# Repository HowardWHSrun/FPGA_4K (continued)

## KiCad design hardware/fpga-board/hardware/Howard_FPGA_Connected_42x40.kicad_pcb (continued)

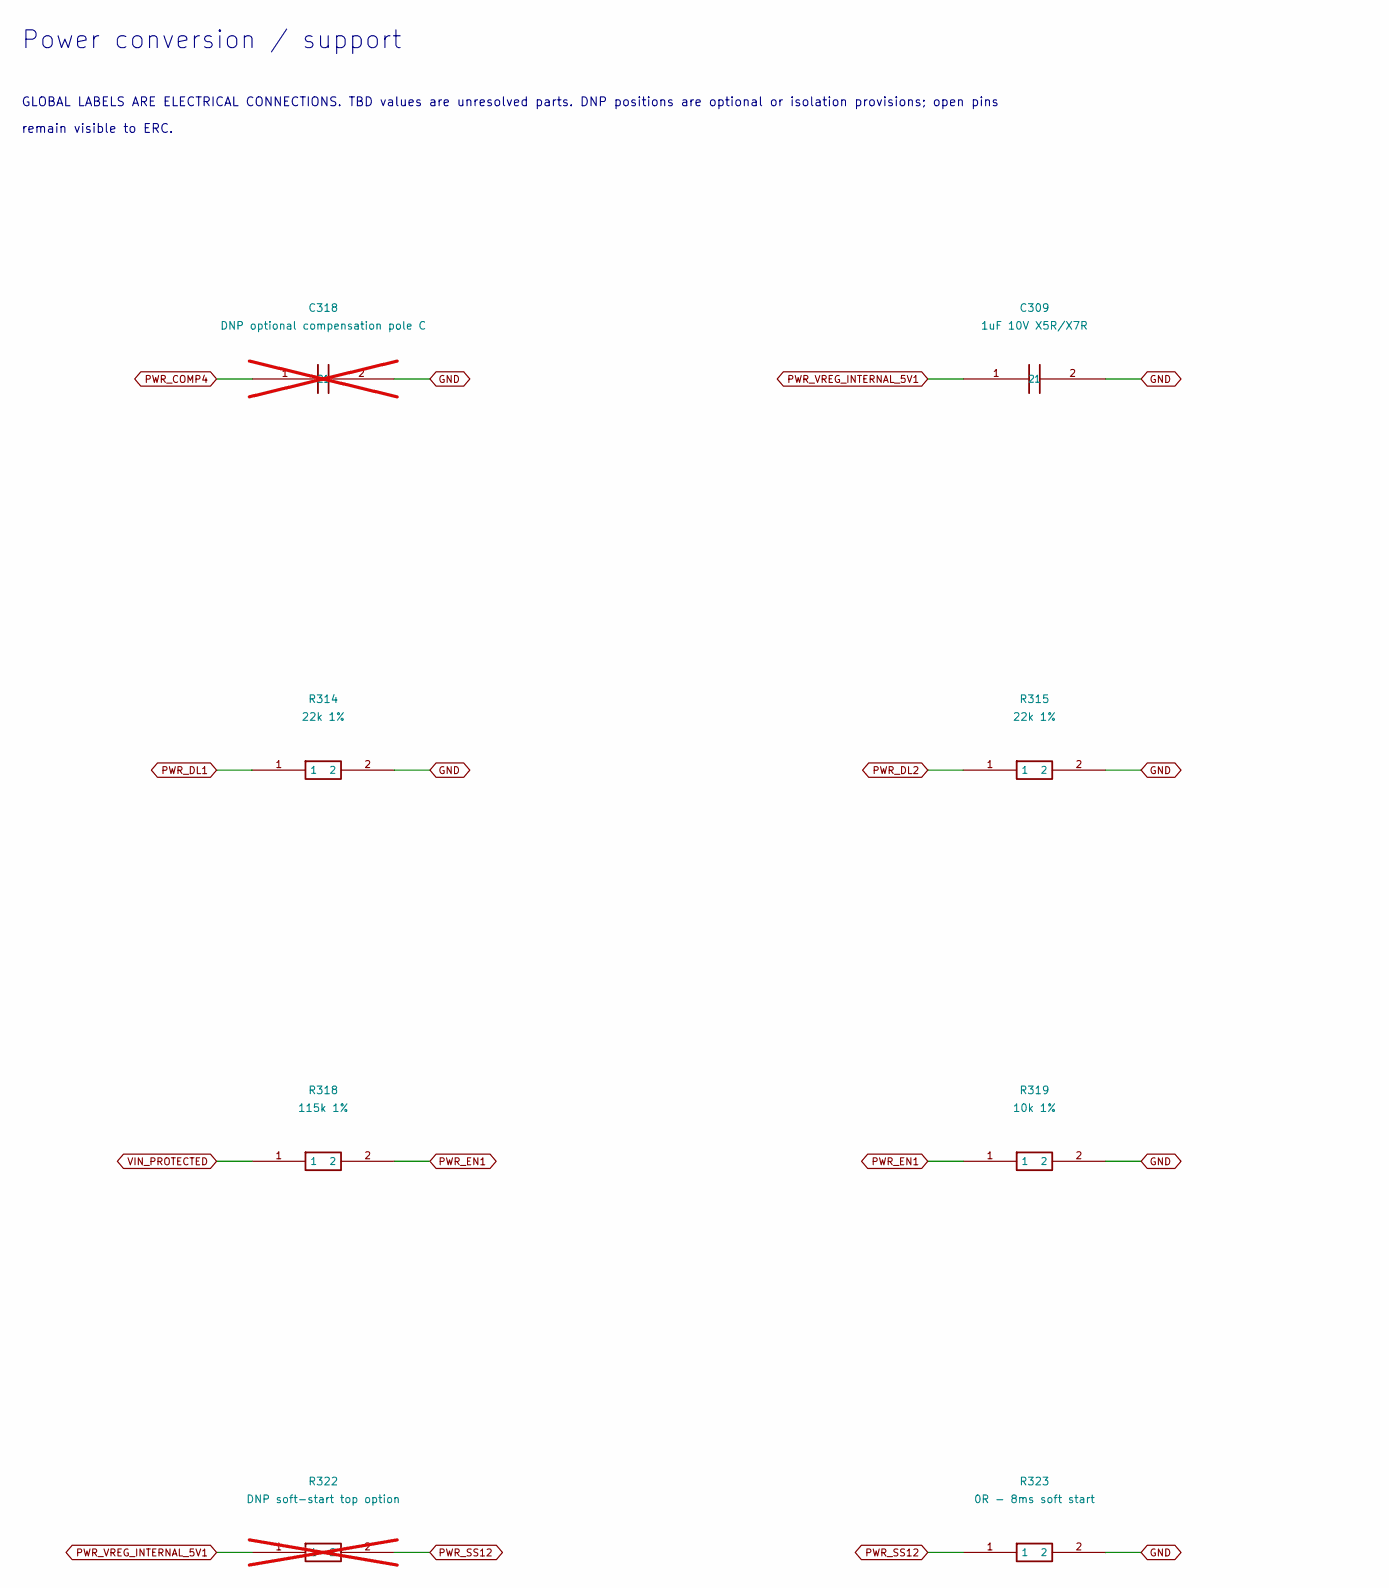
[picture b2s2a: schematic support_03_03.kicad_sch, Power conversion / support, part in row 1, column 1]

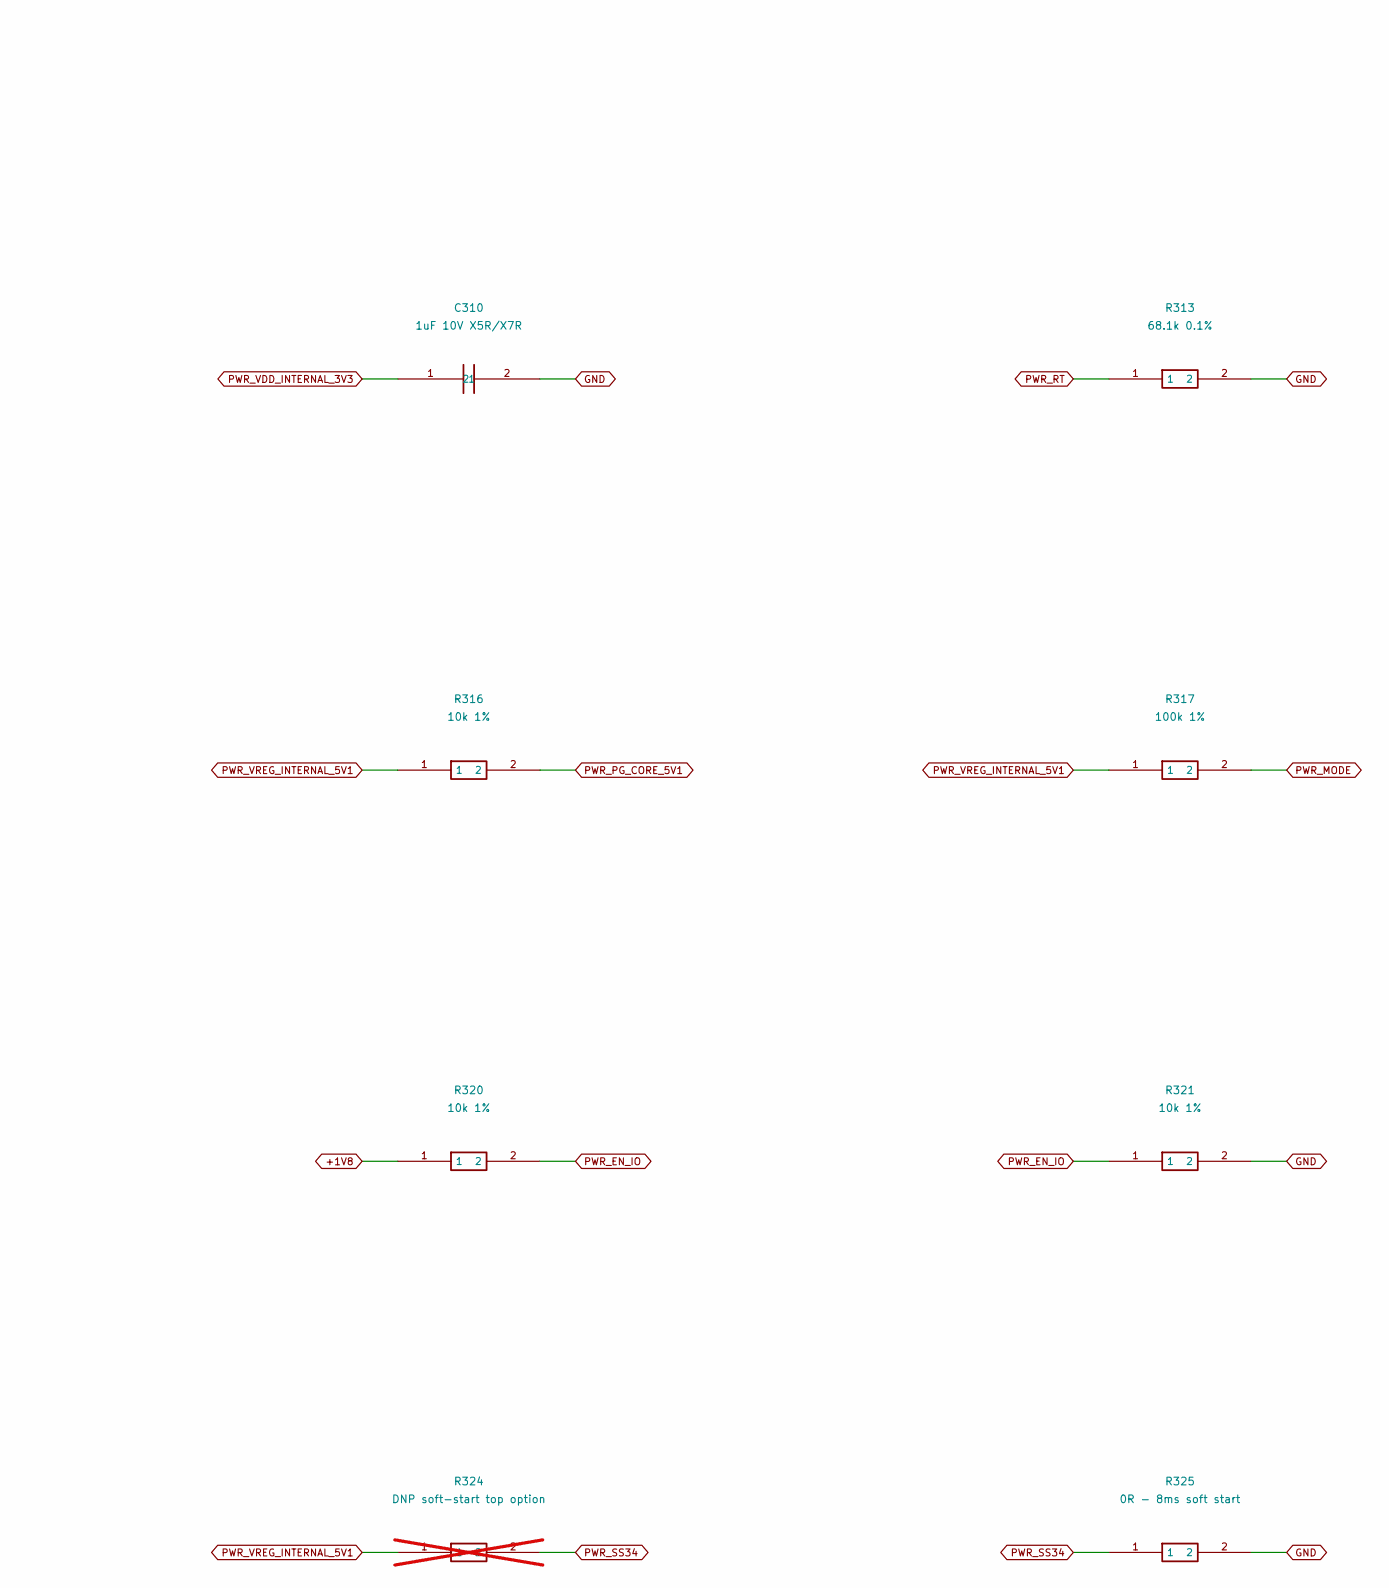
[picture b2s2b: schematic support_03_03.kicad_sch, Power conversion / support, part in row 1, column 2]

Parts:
C309: 1uF 10V X5R/X7R; C_0402_1005Metric__C309; Tolerance TBD; Voltage rating TBD; MPN TBD
C310: 1uF 10V X5R/X7R; C_0402_1005Metric__C310; Tolerance TBD; Voltage rating TBD; MPN TBD
C318: DNP optional compensation pole C; C_0402_1005Metric__C318; Tolerance TBD; Voltage rating TBD; MPN TBD; not fitted
R313: 68.1k 0.1%; R_0402_1005Metric__R313; Tolerance TBD; Voltage rating TBD; MPN TBD
R314: 22k 1%; R_0402_1005Metric__R314; Tolerance TBD; Voltage rating TBD; MPN TBD
R315: 22k 1%; R_0402_1005Metric__R315; Tolerance TBD; Voltage rating TBD; MPN TBD
R316: 10k 1%; R_0402_1005Metric__R316; Tolerance TBD; Voltage rating TBD; MPN TBD
R317: 100k 1%; R_0402_1005Metric__R317; Tolerance TBD; Voltage rating TBD; MPN TBD
R318: 115k 1%; R_0402_1005Metric__R318; Tolerance TBD; Voltage rating TBD; MPN TBD
R319: 10k 1%; R_0402_1005Metric__R319; Tolerance TBD; Voltage rating TBD; MPN TBD
R320: 10k 1%; R_0402_1005Metric__R320; Tolerance TBD; Voltage rating TBD; MPN TBD
R321: 10k 1%; R_0402_1005Metric__R321; Tolerance TBD; Voltage rating TBD; MPN TBD
R322: DNP soft-start top option; R_0402_1005Metric__R322; Tolerance TBD; Voltage rating TBD; MPN TBD; not fitted
R323: 0R - 8ms soft start; R_0402_1005Metric__R323; Tolerance TBD; Voltage rating TBD; MPN TBD
R324: DNP soft-start top option; R_0402_1005Metric__R324; Tolerance TBD; Voltage rating TBD; MPN TBD; not fitted
R325: 0R - 8ms soft start; R_0402_1005Metric__R325; Tolerance TBD; Voltage rating TBD; MPN TBD

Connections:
+1V8: R320.1; also elsewhere on the board
GND: C309.2, C310.2, C318.2, R313.2, R314.2, R315.2, R319.2, R321.2, R323.2, R325.2; also elsewhere on the board
PWR_COMP4: C318.1; also elsewhere on the board
PWR_DL1: R314.1; also elsewhere on the board
PWR_DL2: R315.1; also elsewhere on the board
PWR_EN1: R318.2, R319.1; also elsewhere on the board
PWR_EN_IO: R320.2, R321.1; also elsewhere on the board
PWR_MODE: R317.2; also elsewhere on the board
PWR_PG_CORE_5V1: R316.2; also elsewhere on the board
PWR_RT: R313.1; also elsewhere on the board
PWR_SS12: R322.2, R323.1; also elsewhere on the board
PWR_SS34: R324.2, R325.1; also elsewhere on the board
PWR_VDD_INTERNAL_3V3: C310.1; also elsewhere on the board
PWR_VREG_INTERNAL_5V1: C309.1, R316.1, R317.1, R322.1, R324.1; also elsewhere on the board
VIN_PROTECTED: R318.1; also elsewhere on the board

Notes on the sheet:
GLOBAL LABELS ARE ELECTRICAL CONNECTIONS. TBD values are unresolved parts. DNP positions are optional or isolation provisions; open pins
Power conversion / support
remain visible to ERC.

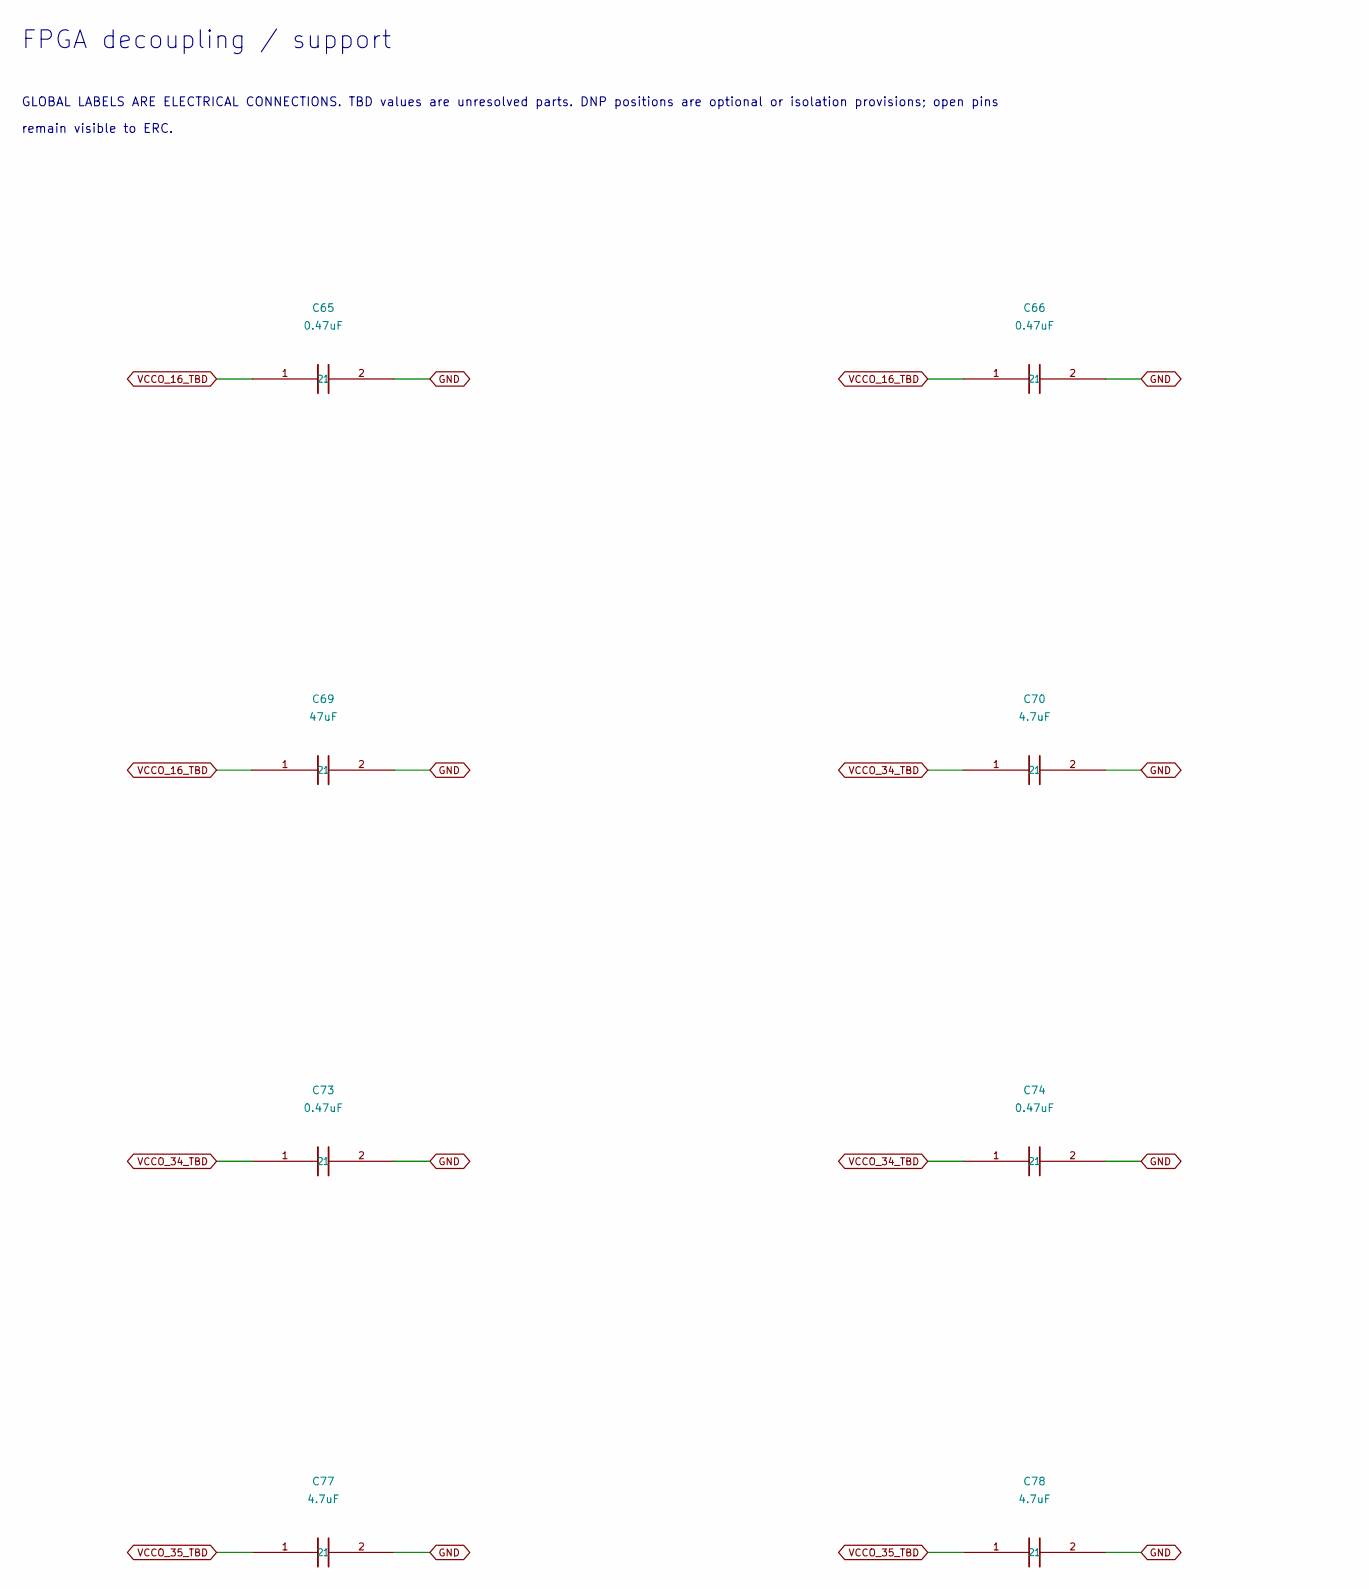
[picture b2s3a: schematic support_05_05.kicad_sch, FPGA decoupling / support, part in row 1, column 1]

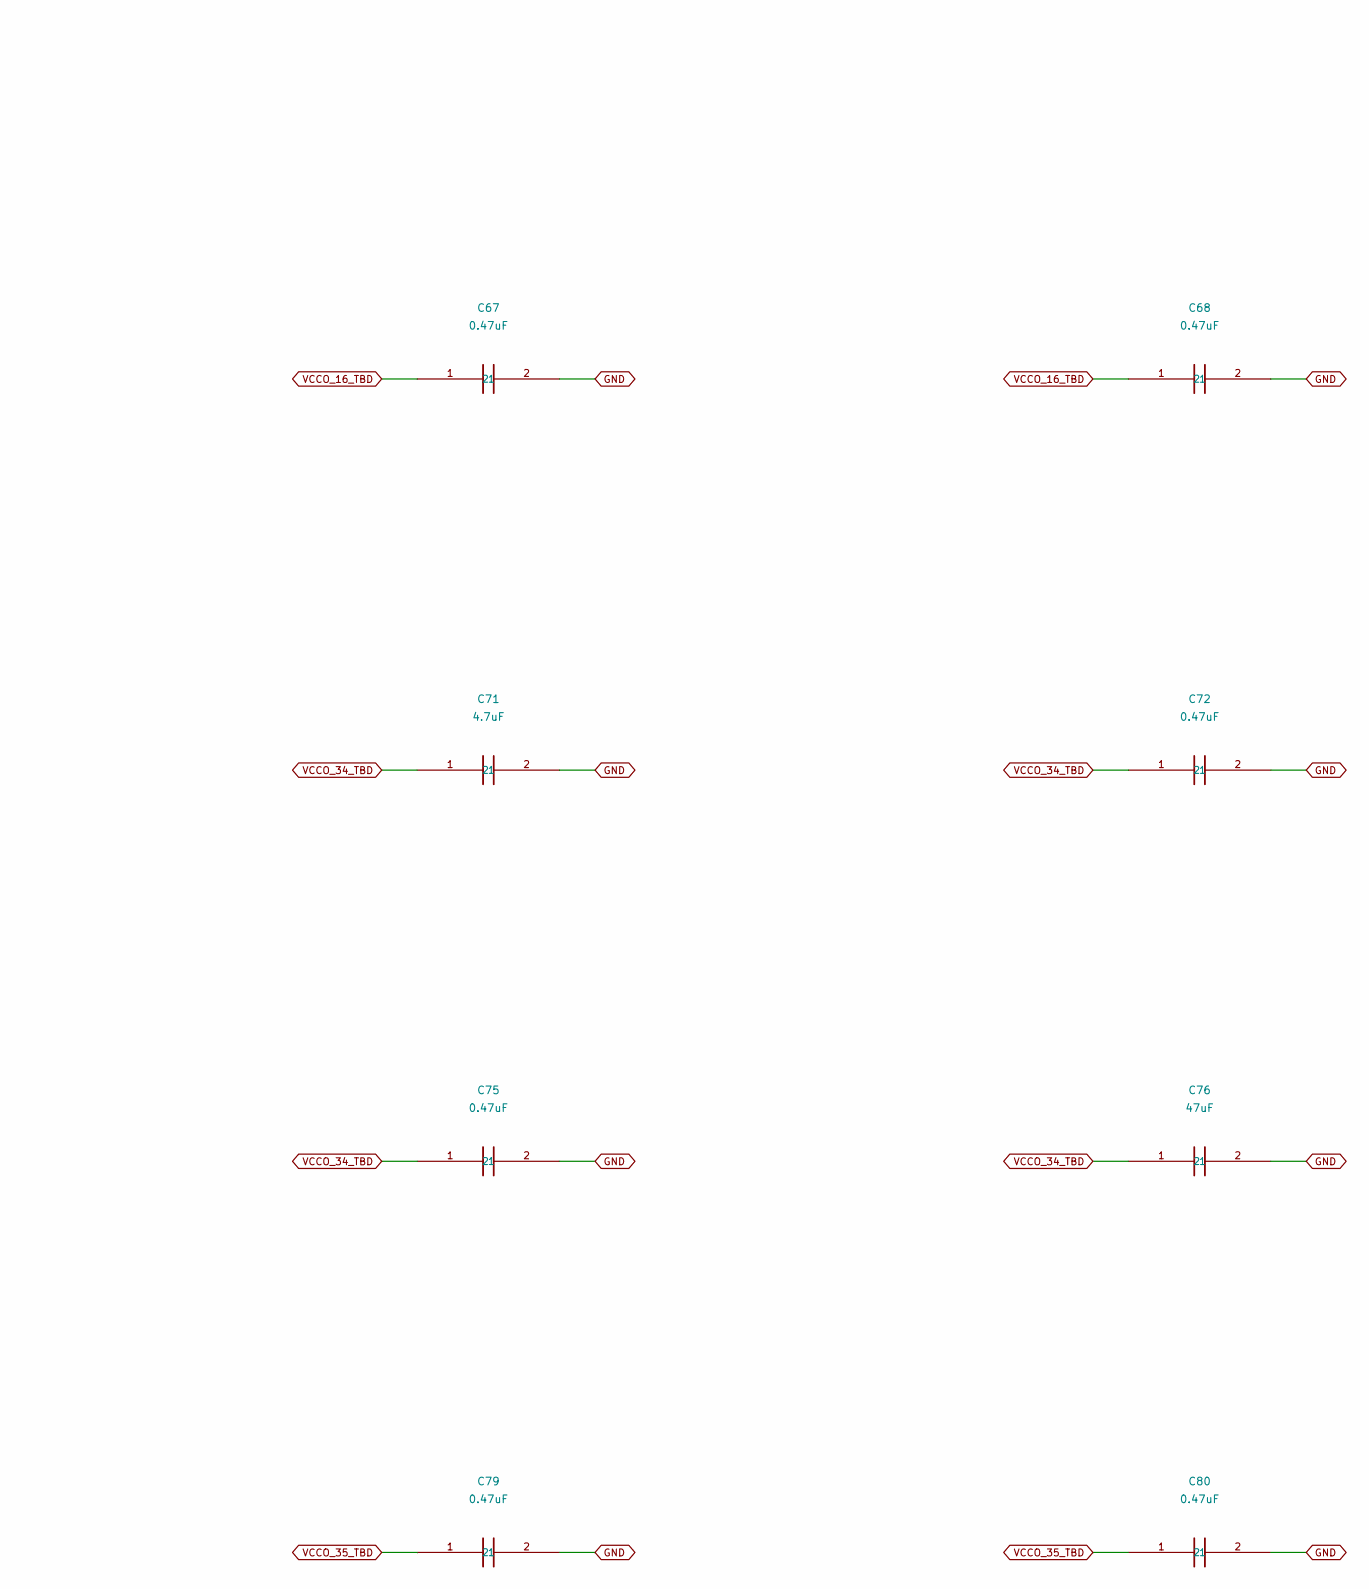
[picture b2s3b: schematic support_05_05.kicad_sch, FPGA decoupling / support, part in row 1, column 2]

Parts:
C65: 0.47uF; C_0201_0603Metric__C65; Tolerance 20%; Voltage rating 10 V; MPN C0603X5R1A474M030BC
C66: 0.47uF; C_0201_0603Metric__C66; Tolerance 20%; Voltage rating 10 V; MPN C0603X5R1A474M030BC
C67: 0.47uF; C_0201_0603Metric__C67; Tolerance 20%; Voltage rating 10 V; MPN C0603X5R1A474M030BC
C68: 0.47uF; C_0201_0603Metric__C68; Tolerance 20%; Voltage rating 10 V; MPN C0603X5R1A474M030BC
C69: 47uF; C_1210_3225Metric__C69; Tolerance TBD; Voltage rating TBD; MPN TBD
C70: 4.7uF; C_0402_1005Metric__C70; Tolerance 10%; Voltage rating 10 V; MPN C1005X5R1A475K050BC
C71: 4.7uF; C_0402_1005Metric__C71; Tolerance 10%; Voltage rating 10 V; MPN C1005X5R1A475K050BC
C72: 0.47uF; C_0201_0603Metric__C72; Tolerance 20%; Voltage rating 10 V; MPN C0603X5R1A474M030BC
C73: 0.47uF; C_0201_0603Metric__C73; Tolerance 20%; Voltage rating 10 V; MPN C0603X5R1A474M030BC
C74: 0.47uF; C_0201_0603Metric__C74; Tolerance 20%; Voltage rating 10 V; MPN C0603X5R1A474M030BC
C75: 0.47uF; C_0201_0603Metric__C75; Tolerance 20%; Voltage rating 10 V; MPN C0603X5R1A474M030BC
C76: 47uF; C_1210_3225Metric__C76; Tolerance TBD; Voltage rating TBD; MPN TBD
C77: 4.7uF; C_0402_1005Metric__C77; Tolerance 10%; Voltage rating 10 V; MPN C1005X5R1A475K050BC
C78: 4.7uF; C_0402_1005Metric__C78; Tolerance 10%; Voltage rating 10 V; MPN C1005X5R1A475K050BC
C79: 0.47uF; C_0201_0603Metric__C79; Tolerance 20%; Voltage rating 10 V; MPN C0603X5R1A474M030BC
C80: 0.47uF; C_0201_0603Metric__C80; Tolerance 20%; Voltage rating 10 V; MPN C0603X5R1A474M030BC

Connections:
GND: C65.2, C66.2, C67.2, C68.2, C69.2, C70.2, C71.2, C72.2, C73.2, C74.2, C75.2, C76.2, C77.2, C78.2, C79.2, C80.2; also elsewhere on the board
VCCO_16_TBD: C65.1, C66.1, C67.1, C68.1, C69.1; also elsewhere on the board
VCCO_34_TBD: C70.1, C71.1, C72.1, C73.1, C74.1, C75.1, C76.1; also elsewhere on the board
VCCO_35_TBD: C77.1, C78.1, C79.1, C80.1; also elsewhere on the board

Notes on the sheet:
GLOBAL LABELS ARE ELECTRICAL CONNECTIONS. TBD values are unresolved parts. DNP positions are optional or isolation provisions; open pins
FPGA decoupling / support
remain visible to ERC.

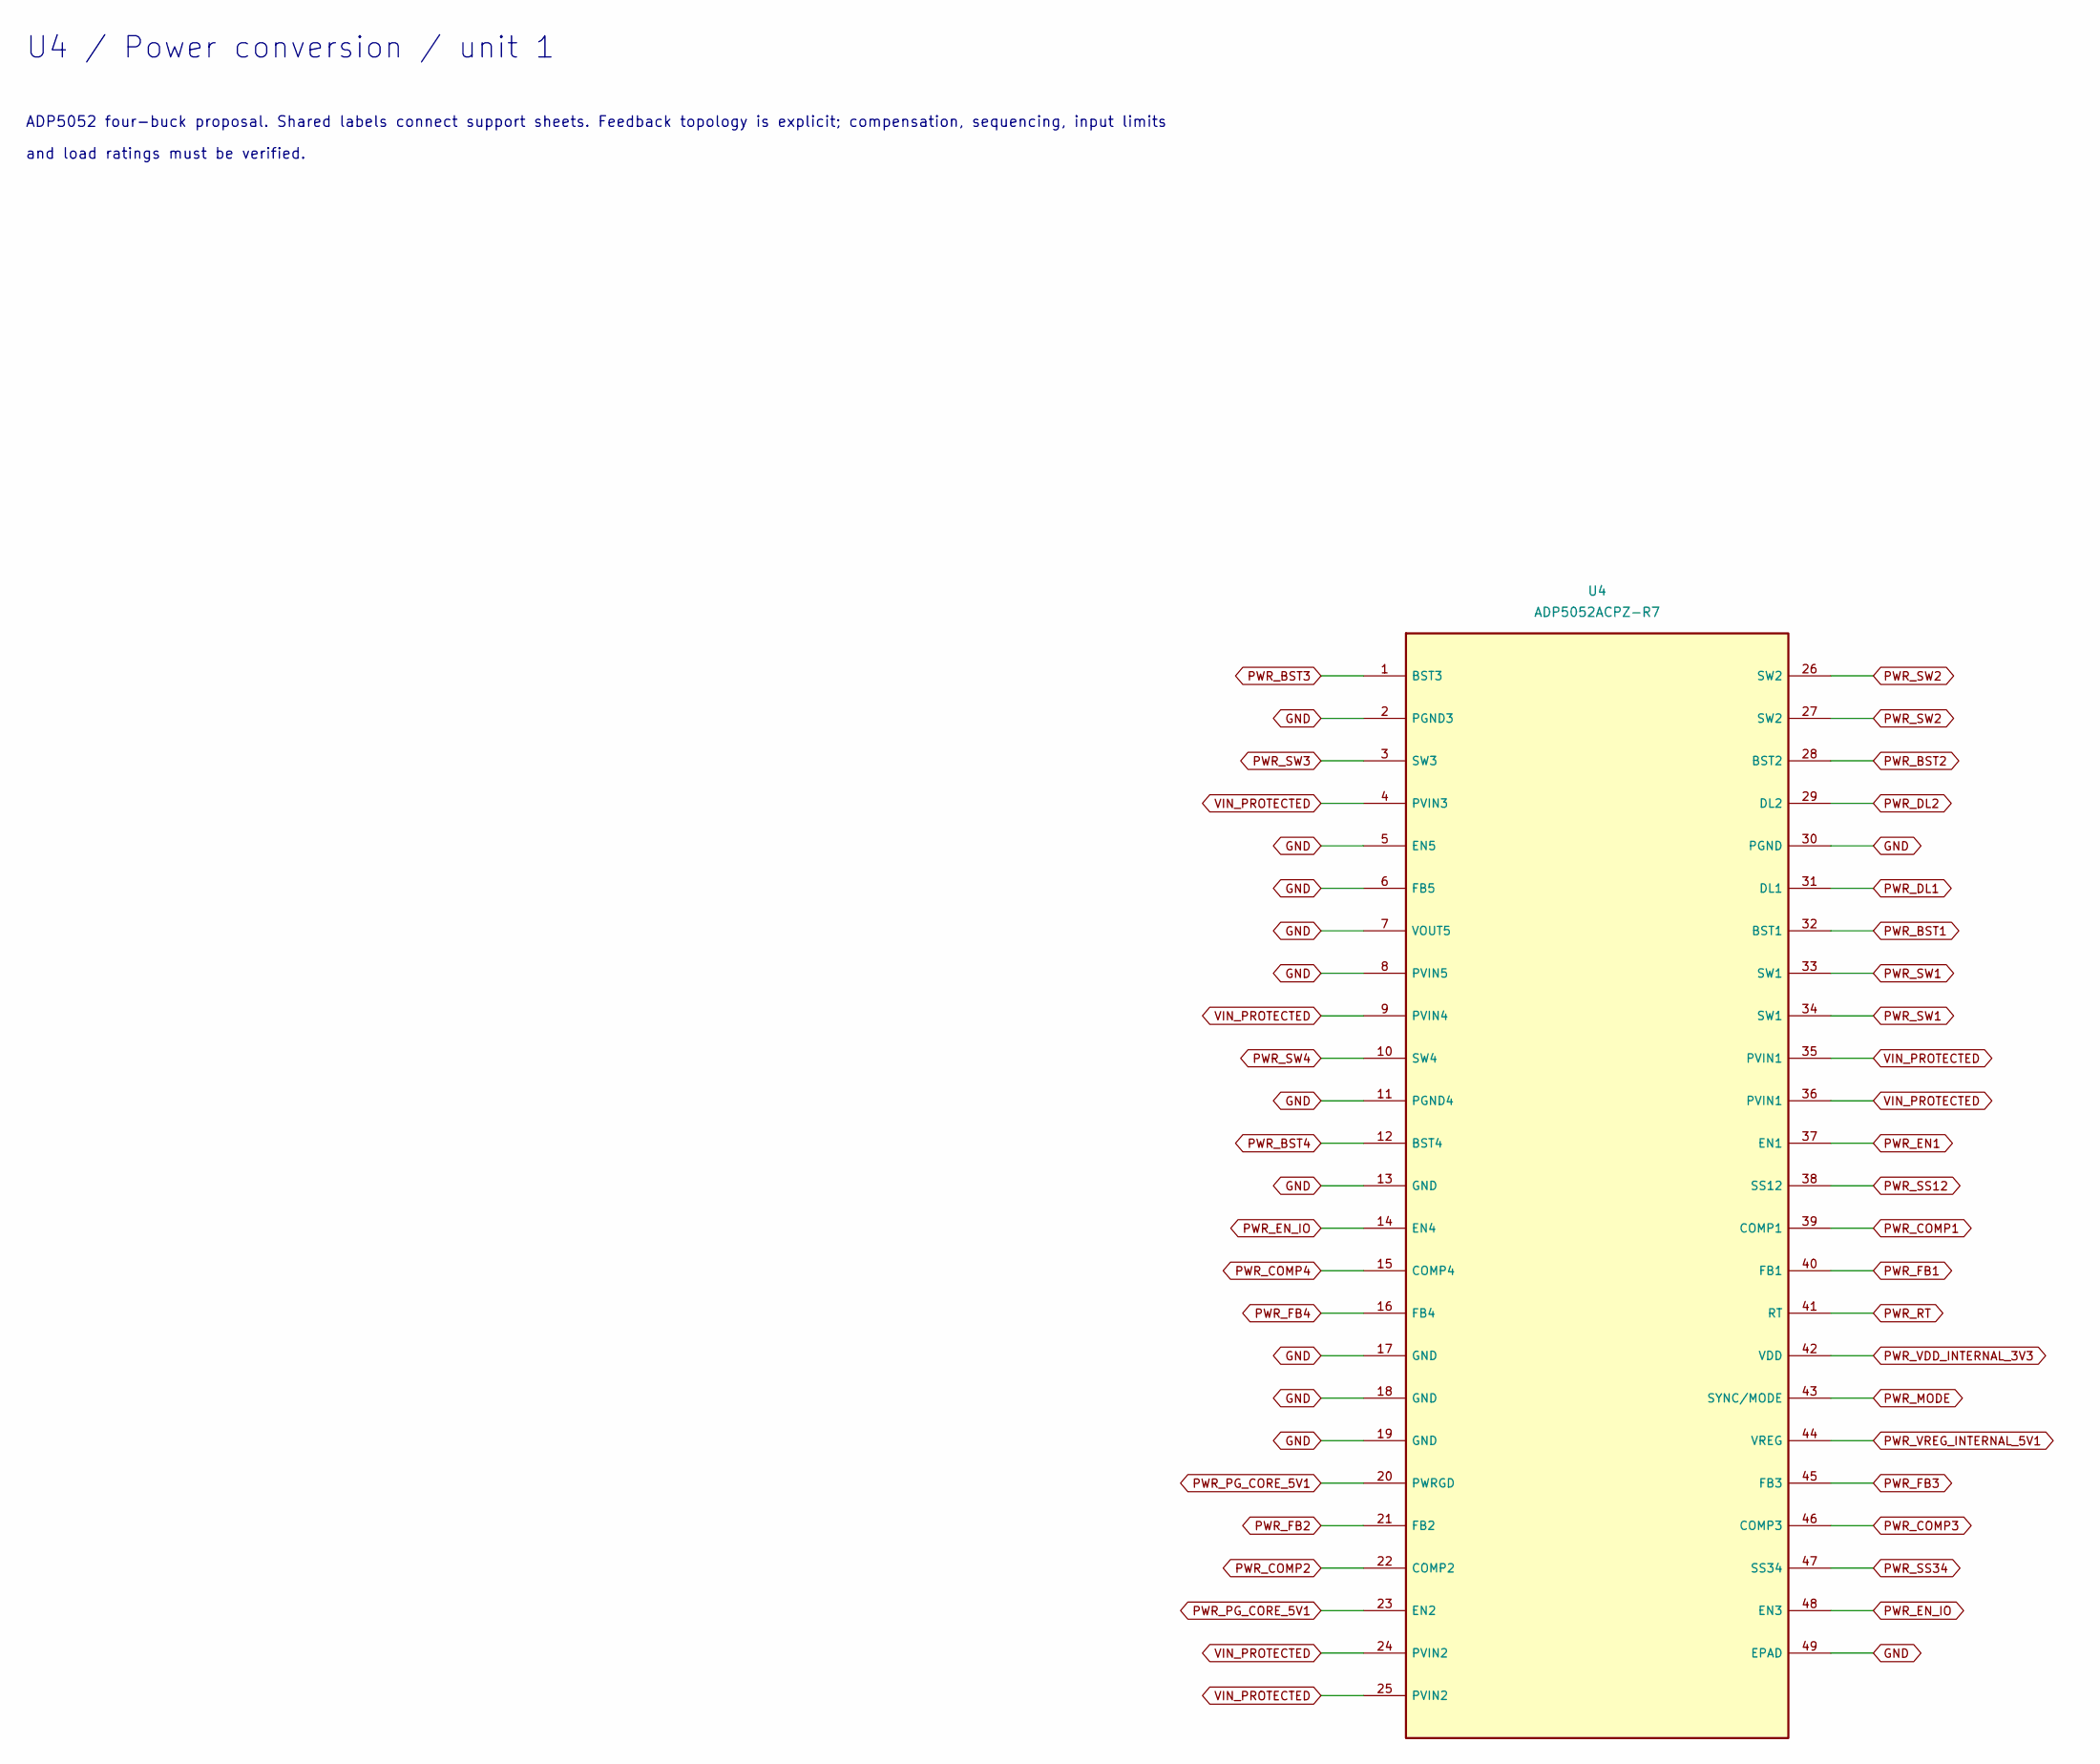
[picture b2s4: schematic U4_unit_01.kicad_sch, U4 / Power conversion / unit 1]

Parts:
U4: ADP5052ACPZ-R7; ADP5052_CP48_13_DRAFT__U4; Tolerance TBD; Voltage rating TBD; MPN ADP5052ACPZ-R7

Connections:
GND: U4.2 (PGND3), U4.5 (EN5), U4.6 (FB5), U4.7 (VOUT5), U4.8 (PVIN5), U4.11 (PGND4), U4.13 (GND), U4.17 (GND), U4.18 (GND), U4.19 (GND), U4.30 (PGND), U4.49 (EPAD); also elsewhere on the board
PWR_BST1: U4.32 (BST1); also elsewhere on the board
PWR_BST2: U4.28 (BST2); also elsewhere on the board
PWR_BST3: U4.1 (BST3); also elsewhere on the board
PWR_BST4: U4.12 (BST4); also elsewhere on the board
PWR_COMP1: U4.39 (COMP1); also elsewhere on the board
PWR_COMP2: U4.22 (COMP2); also elsewhere on the board
PWR_COMP3: U4.46 (COMP3); also elsewhere on the board
PWR_COMP4: U4.15 (COMP4); also elsewhere on the board
PWR_DL1: U4.31 (DL1); also elsewhere on the board
PWR_DL2: U4.29 (DL2); also elsewhere on the board
PWR_EN1: U4.37 (EN1); also elsewhere on the board
PWR_EN_IO: U4.14 (EN4), U4.48 (EN3); also elsewhere on the board
PWR_FB1: U4.40 (FB1); also elsewhere on the board
PWR_FB2: U4.21 (FB2); also elsewhere on the board
PWR_FB3: U4.45 (FB3); also elsewhere on the board
PWR_FB4: U4.16 (FB4); also elsewhere on the board
PWR_MODE: U4.43 (SYNC/MODE); also elsewhere on the board
PWR_PG_CORE_5V1: U4.20 (PWRGD), U4.23 (EN2); also elsewhere on the board
PWR_RT: U4.41 (RT); also elsewhere on the board
PWR_SS12: U4.38 (SS12); also elsewhere on the board
PWR_SS34: U4.47 (SS34); also elsewhere on the board
PWR_SW1: U4.33 (SW1), U4.34 (SW1); also elsewhere on the board
PWR_SW2: U4.26 (SW2), U4.27 (SW2); also elsewhere on the board
PWR_SW3: U4.3 (SW3); also elsewhere on the board
PWR_SW4: U4.10 (SW4); also elsewhere on the board
PWR_VDD_INTERNAL_3V3: U4.42 (VDD); also elsewhere on the board
PWR_VREG_INTERNAL_5V1: U4.44 (VREG); also elsewhere on the board
VIN_PROTECTED: U4.4 (PVIN3), U4.9 (PVIN4), U4.24 (PVIN2), U4.25 (PVIN2), U4.35 (PVIN1), U4.36 (PVIN1); also elsewhere on the board

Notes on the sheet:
and load ratings must be verified.
ADP5052 four-buck proposal. Shared labels connect support sheets. Feedback topology is explicit; compensation, sequencing, input limits
U4 / Power conversion / unit 1

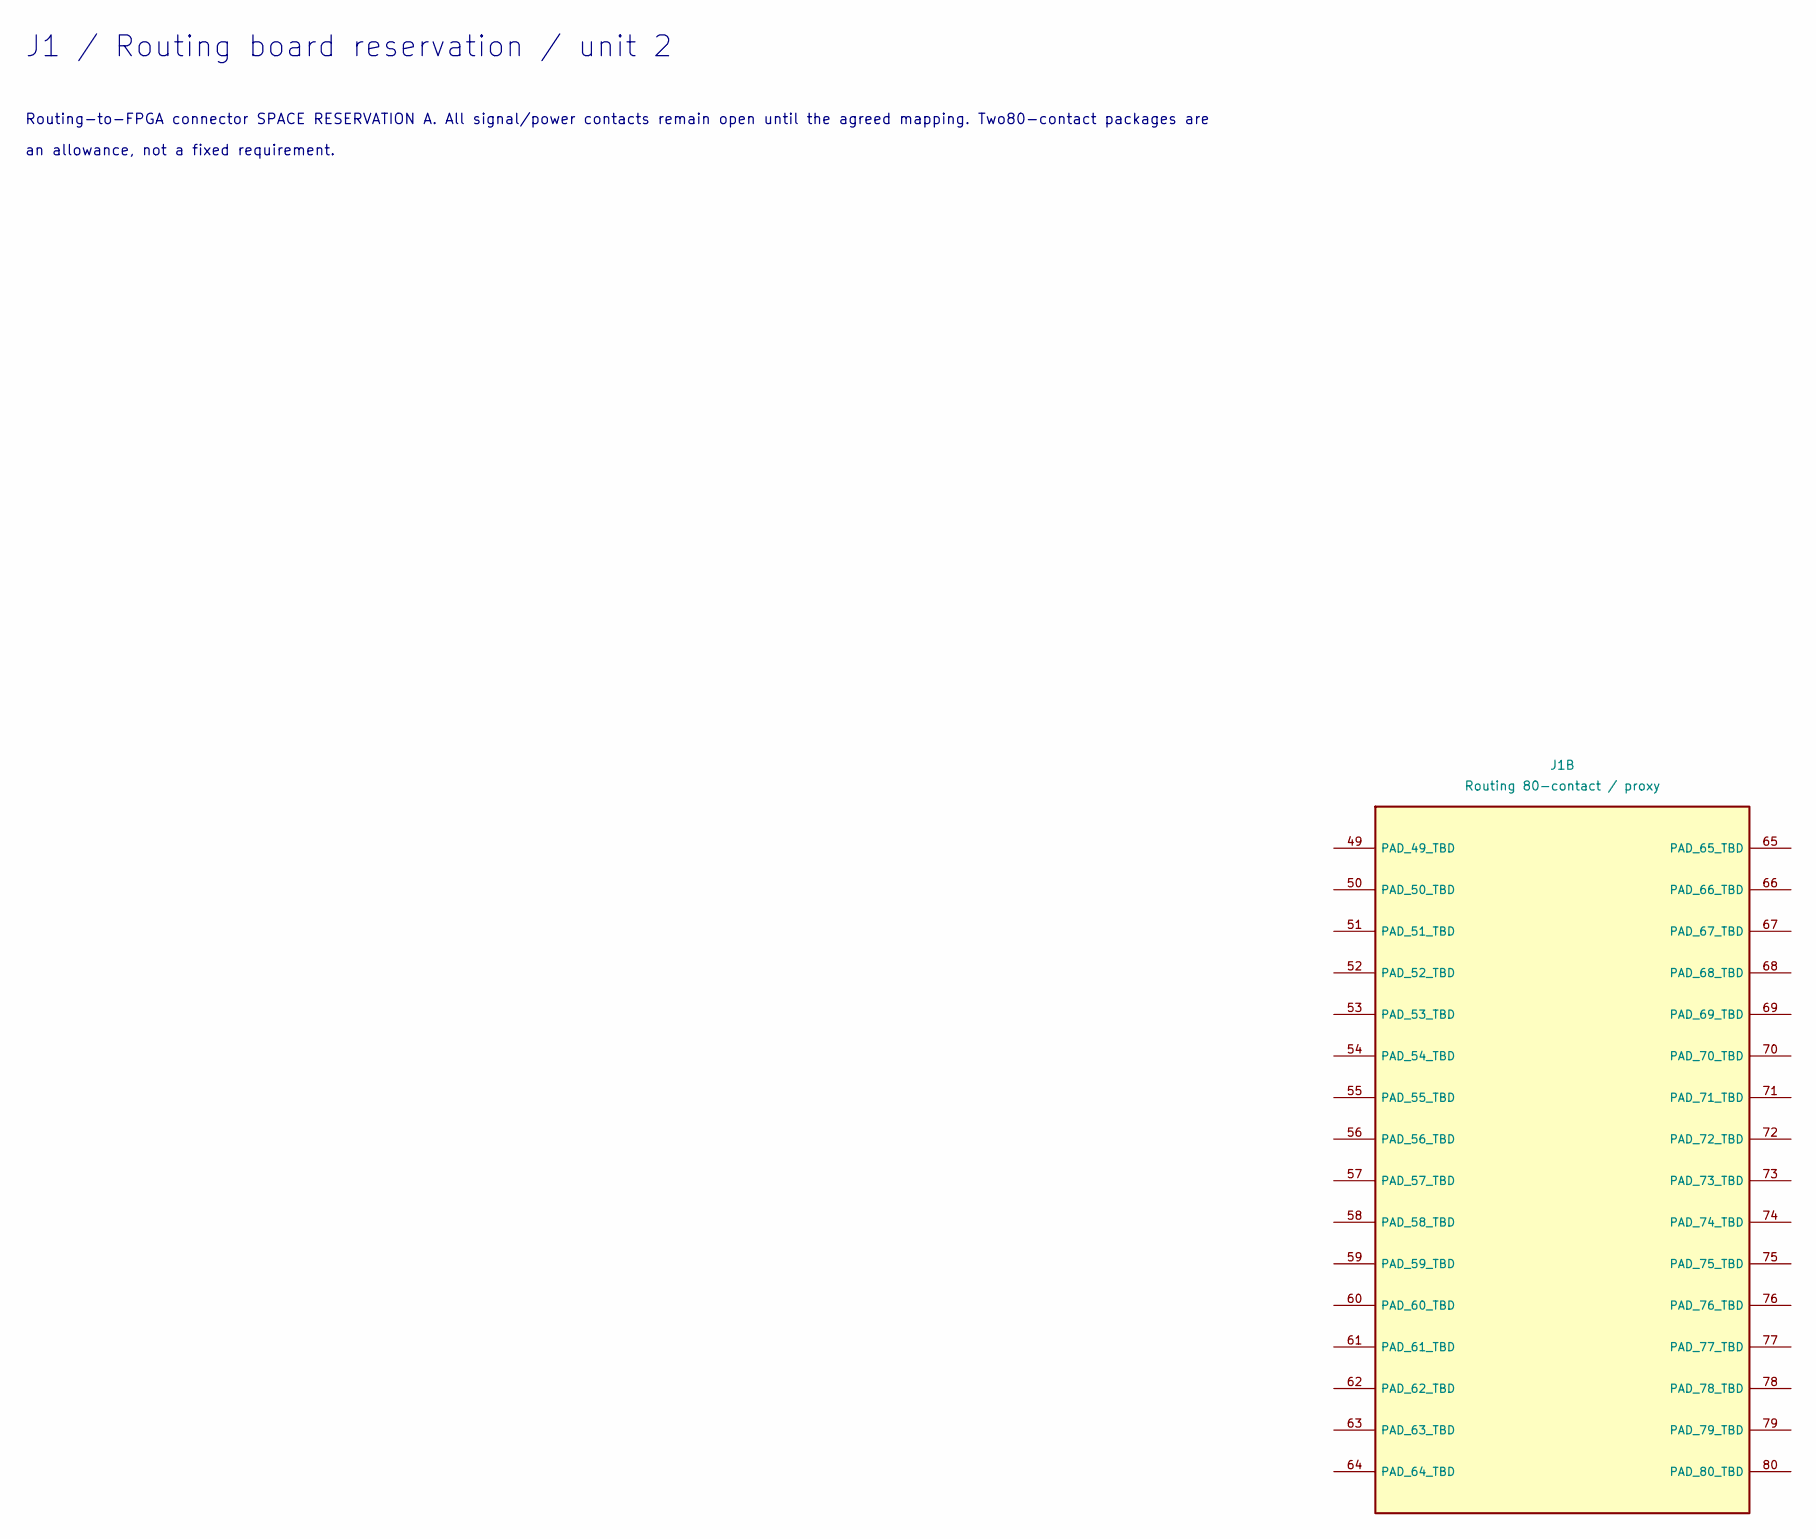
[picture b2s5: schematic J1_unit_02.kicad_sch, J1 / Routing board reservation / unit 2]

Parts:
J1: Routing 80-contact / proxy; Hirose_DF40C-80DS-0.4V_2x40_P0.4mm__J1; Tolerance TBD; Voltage rating TBD; MPN TBD

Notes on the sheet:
Routing-to-FPGA connector SPACE RESERVATION A. All signal/power contacts remain open until the agreed mapping. Two80-contact packages are
J1 / Routing board reservation / unit 2
an allowance, not a fixed requirement.
